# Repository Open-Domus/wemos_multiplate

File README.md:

# Wemos Multiplate

Wemos Multiplate is a modular, ESPHome-powered front plate for Wemos D1 mini and Wemos S2 mini development boards. It combines presence sensing, environmental telemetry, status lighting, and user inputs into a single wall-friendly enclosure.

## Highlights
- Works with Wemos D1 mini (ESP8266) and Wemos S2 mini (ESP32-S2); the S2 mini is strongly recommended if you want every module.
- Integrated 128x64 SSD1306 OLED display with customizable pages.
- Hi-Link LD2410C 24 GHz mmWave presence sensor with optional Bluetooth tuning.
- SHT31-D temperature and humidity probe plus optional BH1750 ambient light and APDS9960 gesture/proximity sensors.
- Two WS2812 addressable LEDs, a piezo buzzer, IR transmitter/receiver, and a header for an external relay module.
- ESPHome package-based configuration lets you enable only the hardware you soldered.

## Repository Layout
- `esphome/` – modular ESPHome configuration split by board (`modules_d1mini/`, `modules_s2mini/`) and shared components (`modules_common/`). Sample automations are under `esphome/automations/`.
- `kicad/wemos-esphome-shield/` – KiCad project, gerbers, STEP models, and release archives for the PCB.

## Hardware Overview
**Base components**
- Wemos D1 mini or Wemos S2 mini dev board (USB-C S2 mini preferred).
- 128x64 I2C OLED display (SSD1306).
- Hi-Link LD2410C mmWave presence sensor.
- Sensirion SHT31-D temperature and humidity sensor.
- Two WS2812 (5 V) addressable LEDs.
- Piezo buzzer with drive transistor.
- TSOP-style IR receiver and 940 nm IR LED pair.

**Optional add-ons**
- BH1750 illuminance sensor.
- APDS9960 gesture/proximity sensor.
- Three front buttons (requires the S2 mini pinout).
- Header for an external 5 V relay module or other accessories.

PCB fabrication files for the latest revision live in `kicad/wemos-esphome-shield/releases/`.

## Getting Started with ESPHome

1. **Install ESPHome**  
   Follow the [ESPHome installation guide](https://esphome.io/guides/installing_esphome.html) (CLI or Home Assistant add-on). CLI examples below assume `pipx install esphome`.

2. **Create secrets**  
   Copy the sample secrets file and edit it with your Wi-Fi and fallback hotspot credentials:
   ```bash
   cp esphome/modules_s2mini/secrets_sample.yaml esphome/secrets.yaml
   ```
   The same `secrets.yaml` is used by both board profiles.

3. **Pick a base profile**  
   - `esphome/multiplate_s2mini.yml` — ESP32-S2 build with every module enabled.  
   - `esphome/multiplate_d1mini.yml` — ESP8266 build with a reduced feature set. Comment out any modules you did not solder to stay within memory limits.

4. **Enable or disable modules**  
   Each module is loaded via the `packages:` section. Comment out a line to disable the corresponding hardware. For example, to skip the gesture sensor:
   ```yaml
   # gesture_sensor: !include modules_common/gesture_sensor.yml
   ```

5. **Build and flash**  
   Connect the board over USB and run:
   ```bash
   esphome run esphome/multiplate_s2mini.yml --device /dev/ttyUSB0
   ```
   After the first successful flash you can go OTA:
   ```bash
   esphome run esphome/your-device-name.yml
   ```

6. **Adopt in Home Assistant**  
   The node exposes all sensors, lights, switches, and buttons via the ESPHome API. Home Assistant will prompt to adopt the new device and automatically create entities.

## Module Reference

| Module                                 | File                                                                        | Notes |
|----------------------------------------|-----------------------------------------------------------------------------|-------|
| Core board setup & Wi-Fi               | `modules_d1mini/common.yml`, `modules_s2mini/common.yml`                    | Handles board selection, Wi-Fi credentials, API, OTA. |
| OLED display, pages, and fonts         | `modules_common/display.yml`, `font/retrogaming.ttf`                        | Provides readout and trend pages with a 4 h temperature graph. |
| LD2410C mmWave presence                | `modules_d1mini/motion_sensor.yml`, `modules_s2mini/motion_sensor.yml`      | Exposes presence, moving/still targets, distance, and Bluetooth control. |
| Temperature & humidity (SHT31-D)       | `modules_common/temp_sensor.yml`                                           | Includes a median filter and linear calibration datapoints. |
| Ambient light (BH1750)                 | `modules_common/light_sensor.yml`                                          | Optional, comment out if the sensor is not populated. |
| Gesture & proximity (APDS9960)         | `modules_common/gesture_sensor.yml`                                        | Optional, provides four gesture binary sensors and calibrated proximity. |
| RGB status LEDs                        | `modules_d1mini/rgb_leds.yml`, `modules_s2mini/rgb_leds.yml`                | Two WS2812 LEDs mapped in the sample automations. |
| Buzzer                                 | `modules_d1mini/buzzer.yml`, `modules_s2mini/buzzer.yml`                    | Template buttons trigger predefined alert patterns. |
| IR transmitter/receiver                | `modules_d1mini/ir_remote.yml`, `modules_s2mini/ir_remote.yml`             | Exposes `ir_remote` transmitter ID and raw receiver for learning codes. |
| Relay header                           | `modules_d1mini/relay.yml`, `modules_s2mini/relay.yml`                      | Optional GPIO-controlled 5 V relay output. |
| Front buttons (S2 mini only)           | `modules_s2mini/buttons.yml`                                               | Three debounced GPIO inputs. |
| Automations (display & LEDs)           | `automations/display_motion.yml`, `automations/motion_status_leds.yml`      | Opt-in template switches to toggle display blanking and LED indicators. |

## Built-in Automations
- `display_motion` keeps the OLED blank until motion is detected, then shows the readout page.
- `motion_status_leds` maps moving and still target detection to the two WS2812 LEDs.

Enable or disable these from the `packages:` block just like the hardware modules.

## Tuning the LD2410C mmWave Sensor
1. Enable the Bluetooth switch entity (`*-ld2410-bluetooth`) exposed by ESPHome.
2. Use the official Android configuration app: <https://play.google.com/store/apps/details?id=com.hlk.hlkradartool>.
3. Connect to the sensor, enter Engineering Mode, and adjust the eight detection gates to match your room layout. Lower values increase sensitivity.
4. Apollo Automation maintains a detailed tuning guide: <https://wiki.apolloautomation.com/books/msr-1/page/how-to-tune-mmwave-using-home-assistant>.

Keeping the heavy tuning UI out of ESPHome reduces load on the D1 mini and shortens boot times.

## Using the IR Remote
Add climate, media, or switch components to your ESPHome profile and reference the shared `ir_remote` transmitter and `ir_rx` receiver IDs. Example:

```yaml
climate:
  - platform: daikin
    name: ${device_name}-climate
    transmitter_id: ir_remote
    receiver_id: ir_rx
```

Use the `remote_receiver` in learning mode (`dump: raw`) to capture codes from your existing remote.

## Manufacturing Files
- Latest gerber sets: `kicad/wemos-esphome-shield/gerber/`
- STEP models for enclosure work: `kicad/wemos-esphome-shield/step/`
- Release bundles (gerbers, BOM, pick-and-place): `kicad/wemos-esphome-shield/releases/`

Send the gerber ZIP to your PCB manufacturer of choice, then populate the board according to the silkscreen and BOM in the release archive.

---

Questions, improvements, or pull requests are welcome!

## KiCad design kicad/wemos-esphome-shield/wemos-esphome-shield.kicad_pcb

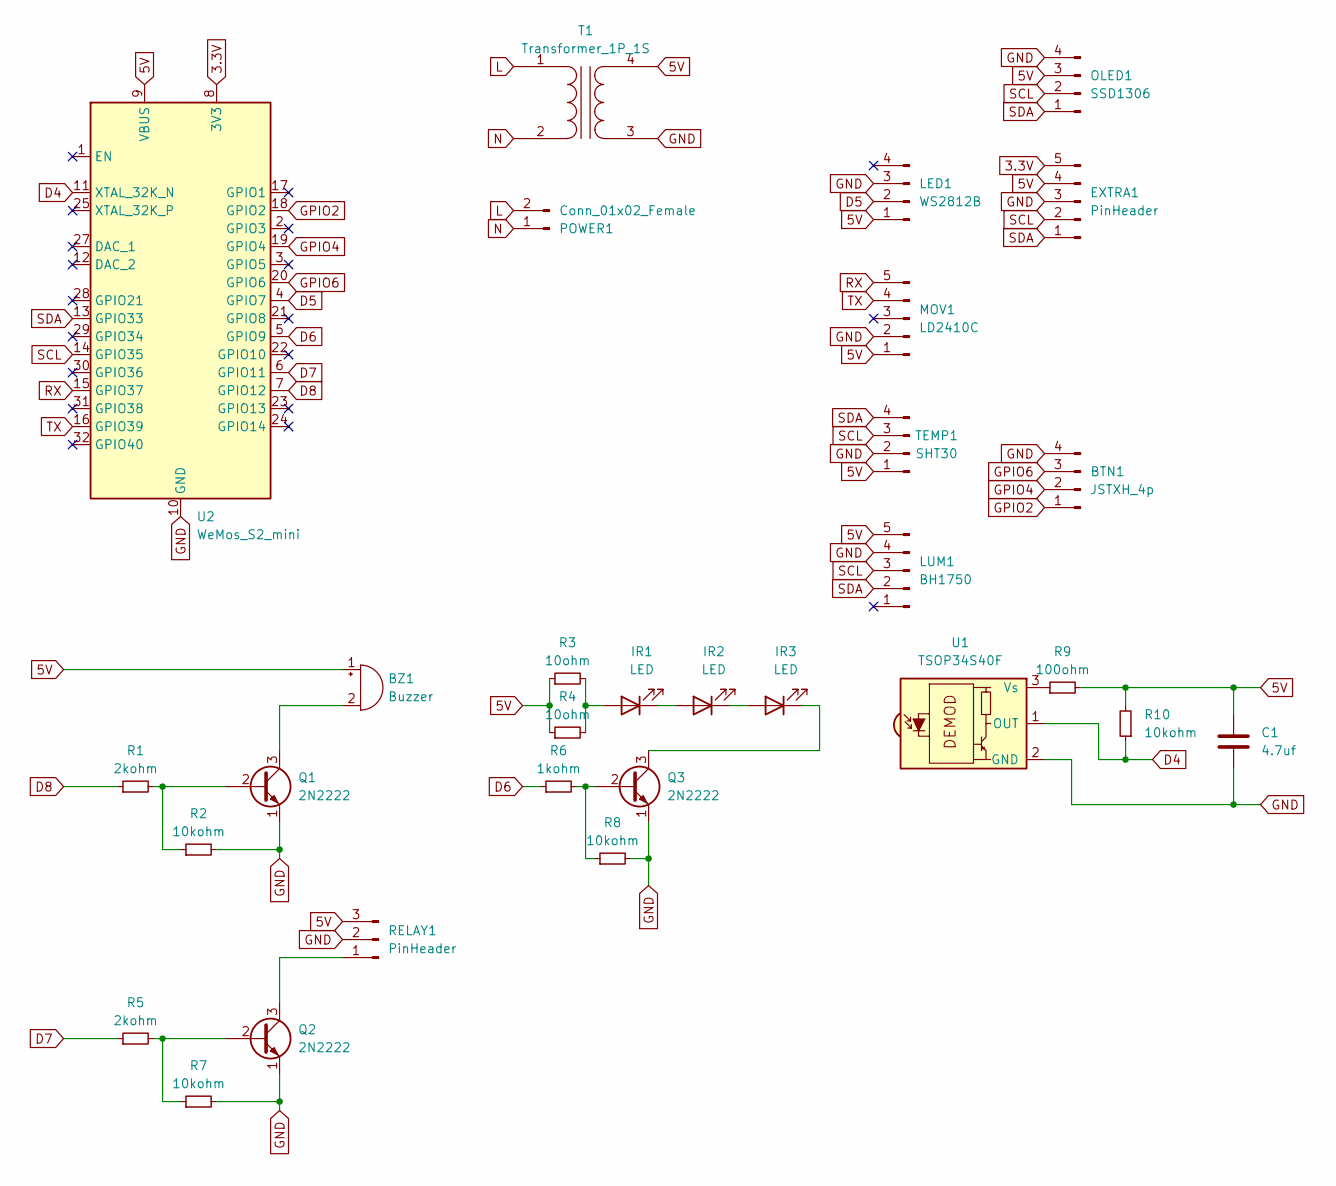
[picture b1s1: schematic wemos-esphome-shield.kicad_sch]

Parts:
BTN1: JSTXH_4p; JST_XH_B4B-XH-A_1x04_P2.50mm_Vertical
BZ1: Buzzer; Buzzer_12x9.5RM7.6
C1: 4.7uf; C_1206_3216Metric_Pad1.33x1.80mm_HandSolder
EXTRA1: PinHeader; PinHeader_1x05_P2.54mm_Vertical
IR1, IR2, IR3: LED; LED_D5.0mm
LED1: WS2812B; LED breakout
LUM1: BH1750
MOV1: LD2410C
OLED1: SSD1306; SSD1306 OLED 128x64
POWER1: Conn_01x02_Female; TerminalBlock_MetzConnect_Type094_RT03502HBLU_1x02_P5.00mm_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
Q1, Q2, Q3: 2N2222; SOT-23_Handsoldering
R1, R5: 2kohm; R_1206_3216Metric_Pad1.30x1.75mm_HandSolder
R2, R7, R8, R10: 10kohm; R_1206_3216Metric_Pad1.30x1.75mm_HandSolder
R3, R4: 10ohm; R_1206_3216Metric_Pad1.30x1.75mm_HandSolder
R6: 1kohm; R_1206_3216Metric_Pad1.30x1.75mm_HandSolder
R9: 100ohm; R_1206_3216Metric_Pad1.30x1.75mm_HandSolder
RELAY1: PinHeader; PinHeader_1x03_P2.54mm_Vertical
T1: Transformer_1P_1S; 220v AC to 5v DC Transformer
TEMP1: SHT30; JST_XH_B4B-XH-A_1x04_P2.50mm_Vertical
U1: TSOP34S40F; Vishay_MOLD-3Pin
U2: WeMos_S2_mini; WEMOS_S2_mini

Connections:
3.3V: EXTRA1.5, U2.8 (3V3)
5V: BZ1.1 (+), C1.1, EXTRA1.4, LED1.1, LUM1.5, MOV1.1, OLED1.3, R3.1, R4.1, R9.2, R10.2, RELAY1.3, T1.4 (SB), TEMP1.1, U2.9 (VBUS)
D4: R10.1, U1.1 (OUT), U2.11 (XTAL_32K_N)
D5: LED1.2, U2.4 (GPIO7)
D6: R6.1, U2.5 (GPIO9)
D7: R5.1, U2.6 (GPIO11)
D8: R1.1, U2.7 (GPIO12)
GND: BTN1.4, C1.2, EXTRA1.3, LED1.3, LUM1.4, MOV1.2, OLED1.4, Q1.1 (E), Q2.1 (E), Q3.1 (E), R2.2, R7.2, R8.2, RELAY1.2, T1.3 (SA), TEMP1.2, U1.2 (GND), U2.10 (GND), U2.26 (GND)
GPIO2: BTN1.1, U2.18 (GPIO2)
GPIO4: BTN1.2, U2.19 (GPIO4)
GPIO6: BTN1.3, U2.20 (GPIO6)
L: POWER1.2, T1.1 (AA)
N: POWER1.1, T1.2 (AB)
unnamed: BZ1.2 (-), Q1.3 (C)
unnamed: IR1.2 (A), R3.2, R4.2
unnamed: IR1.1 (K), IR2.2 (A)
unnamed: IR2.1 (K), IR3.2 (A)
unnamed: IR3.1 (K), Q3.3 (C)
unnamed: Q1.2 (B), R1.2, R2.1
unnamed: Q2.2 (B), R5.2, R7.1
unnamed: Q2.3 (C), RELAY1.1
unnamed: Q3.2 (B), R6.2, R8.1
unnamed: R9.1, U1.3 (Vs)
RX: MOV1.5, U2.15 (GPIO37)
SCL: EXTRA1.2, LUM1.3, OLED1.2, TEMP1.3, U2.14 (GPIO35)
SDA: EXTRA1.1, LUM1.2, OLED1.1, TEMP1.4, U2.13 (GPIO33)
TX: MOV1.4, U2.16 (GPIO39)

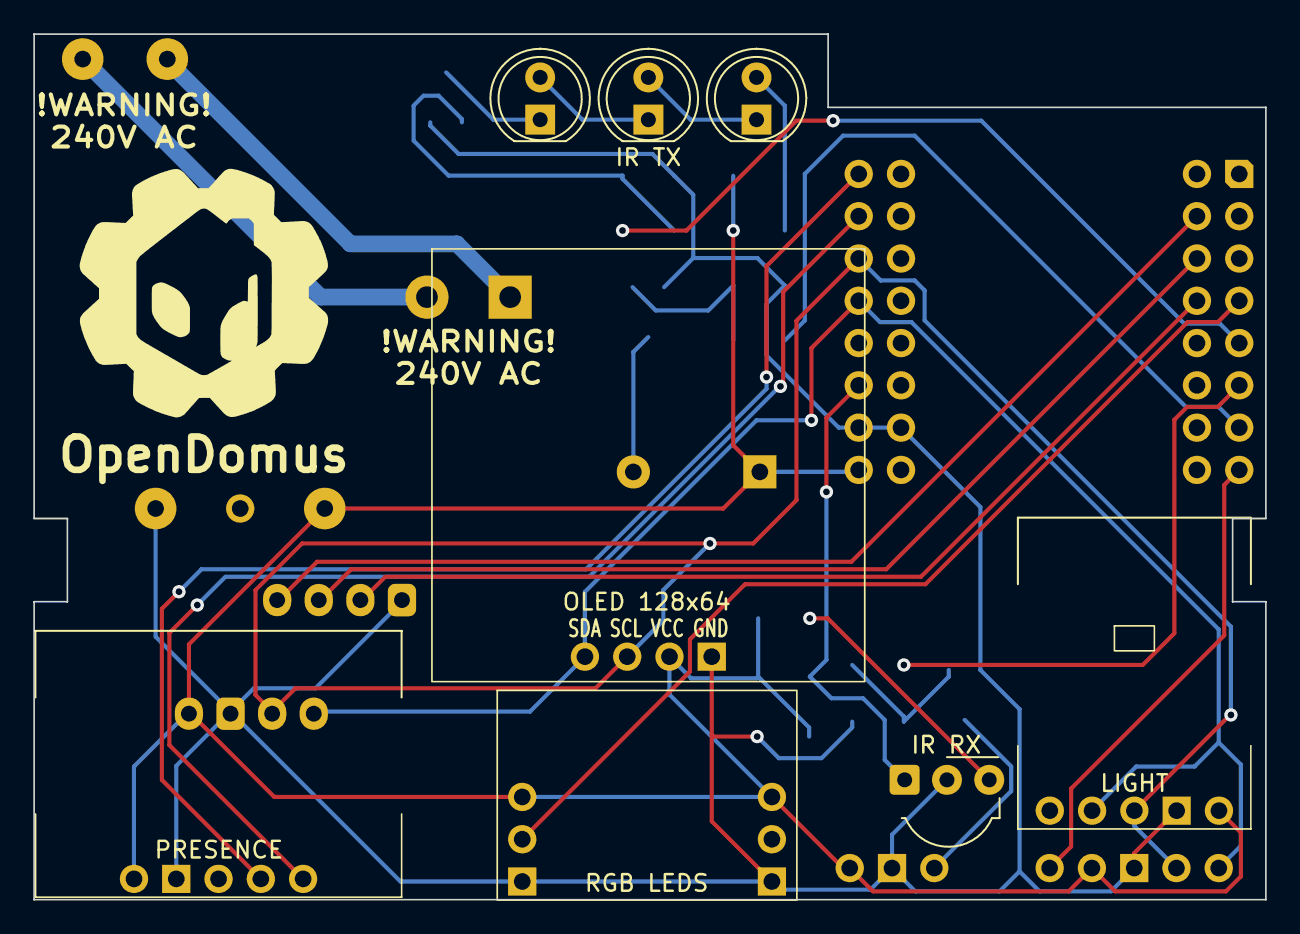
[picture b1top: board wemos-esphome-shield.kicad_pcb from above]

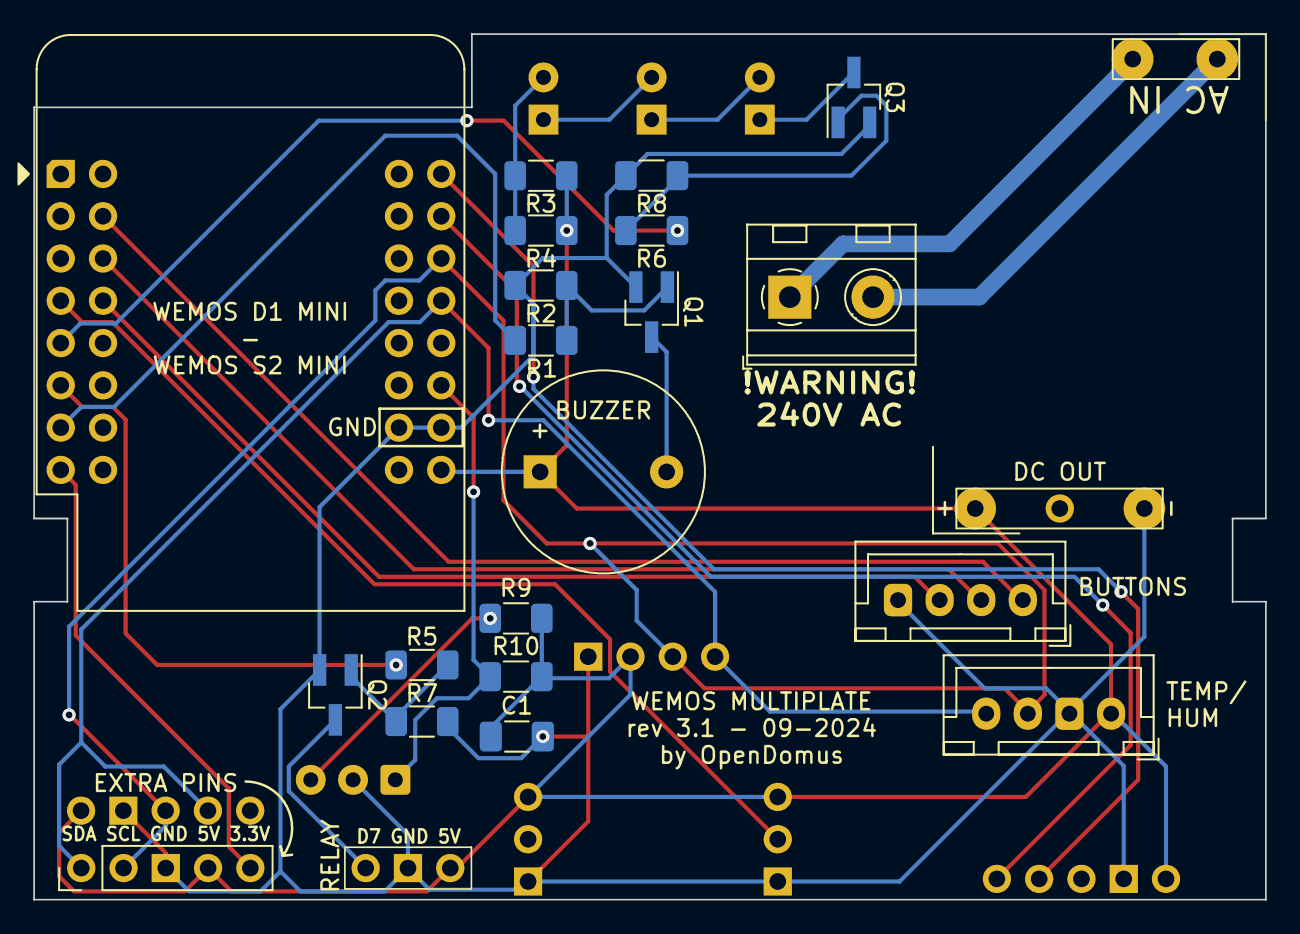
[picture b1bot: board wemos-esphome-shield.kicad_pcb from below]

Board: 2 copper layers, 74.0 x 52.0 mm, 30 parts (22 on the bottom side), 27 nets.

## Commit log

2023-03-30 move sensors and relay2
2023-03-30 fix leds footprint
2023-04-06 Fix some electrical net, new cut edge, new netclasses
2023-04-06 first routing version
2023-04-07 add yaml files
2023-04-07 update gitignore
2023-04-07 update APDS footprint for future compatibility
2023-04-14 transistor driven relay pin, expose more extra pins, and routing
2023-04-17 add oled screen pads
2023-04-18 change temp sensor in yml
2023-04-18 fix logos
2023-04-19 updated confs for apds9960
2023-04-19 added archives for rev1
2023-04-19 fix schema and routing for APDS9960
2023-05-04 updated confs for rgb leds
2023-05-05 updated confs for PIR
2023-05-05 updated confs for display
2023-05-06 added component step files
2023-05-11 add hyphens to device names, add svg
2023-05-14 modularize yaml config
2023-05-14 fix modules
2023-05-15 turn off display after 120s of no motion
2023-09-26 fixes for esphome 2023.8
2024-01-31 footprint fixes
2024-02-16 new footprints
2024-02-16 fix footprints and schematic
2024-02-16 update schematic
2024-03-10 add secrets_sample.yaml
2024-03-10 fix esphome yaml for revision 2
2024-03-10 cleanup yaml round 1
2024-03-12 update schematics
2024-03-13 update footprints
2024-03-13 first positioning of footprints
2024-03-13 wire tracks
2024-03-13 rev2 sent to jlcpcb
2024-03-14 route gesture sensor to 3.3v power
2024-03-29 custom SOT-23 footprint and other small adjustments
2024-03-29 center oled display
2024-03-29 rev2.1 sent to jlcpcb
2024-04-11 edit yml files for revision 2.2
2024-04-11 reroute buzzer to D8
2024-04-12 cleanup readme and yml files
2024-04-12 add step file and update readme
2024-04-13 move stuff around
2024-04-13 rev2.2 sent to jlcpcb
2024-04-18 fix some tracks
2024-04-22 add rendering to readme
2024-04-22 use relative path
2024-04-22 add features to readme
2024-04-23 add automations folder (wip)
2024-04-23 remove test
2024-04-23 add tool versions
2024-05-03 expose copies of motion sensors to make automations compile
2024-05-08 fix motion automation and proximity sensor calibration
2024-05-20 rename light module to rgb_leds
2024-05-21 split display module in 2 versions
2024-05-21 more cleanup
2024-05-21 update main yml
2024-05-21 readme
2024-05-21 small display fixes
2024-05-21 add median filter to sensors
2024-06-12 small updates
2024-06-12 reset gesture sensor defaults
2024-06-30 move pcb references
2024-07-01 split modules for wemos and lolin
2024-07-04 add ota platform
2024-07-15 fix gitignore
2024-07-15 fix s2 mini buzzer pin
2024-07-16 fix readme and rename wemos D1 template file
2024-07-21 fix relay pin on wemos s2 mini
2024-07-21 cleanup libraries
2024-08-13 add buttons module
2024-08-18 added buttons and ir receiver. rerouted everything
2024-08-18 Fix PCB to use Wemos S2 mini (#2)
    * cleanup libraries
    * added buttons and ir receiver. rerouted everything
2024-08-18 add ir receiver
2024-08-18 drop support for 128x32 oled display
2024-08-19 rev3 sent to jlcpcb
2025-08-10 fix display: reposition and show temp graph
2025-09-22 cleanup kicad
2025-09-22 add switches to toggle automations
2025-09-22 togglable automations fixes
2025-09-23 rework readme file
2025-09-23 fix bug in buttons.yml
2025-09-23 motion activated relay plugin
2025-11-11 board specific improvements and updates for esphome 2025.10.4
2025-11-11 add .venv dir to gitignore
2025-11-29 add raw temp sensor and calibration
2026-02-27 wemos add restore from flash
